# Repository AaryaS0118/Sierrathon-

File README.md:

# Sierrathon PCB Design – Pocket Lab

KiCad 10 project for the Sierrathon PCB design hackathon.
Pocket Lab: a keyring-sized USB logic analyzer / voltmeter for engineering students.
Specs, BOM and scoring live in `Resources/`.

## Board outline (done)
- Rounded stick, 75 x 27 mm, 3 mm corners. USB-C on BOTH ends:
  J1 (left, silkscreen "PC") goes to the laptop, J2 (right, silkscreen "PROBE") goes to the circuit under test.
- M4 holes sit right behind each USB-C so the screws take plug-in force:
  MH1/MH3 at (13, 6)/(13, 21), MH2/MH4 at (62, 6)/(62, 21). MH4 doubles as the keyring hole.
  Coordinates are mm from the board's top-left (grid origin is set there).
- Blue drawings on `User.Comments` are placement guides only (J1, J2, RP2040 zone, LED zone,
  R20-R25 zone, hole circles). Delete them once parts are placed.

## Probe port J2 (judges approved adding a USB-C)
J2 is the SAME part as J1 (UJ20-C-H-G-SMT-TR), so no new footprint. Each signal goes through
a 1 kΩ series resistor (R20-R25, same part as R7/R8: RC0402FR-071KL) placed close to J2.

| J2 pins | Net | RP2040 |
|---|---|---|
| A6 + B6 (D+, tied together) | CH0 | GPIO0 (pin 2) |
| A7 + B7 (D-, tied together) | CH1 | GPIO1 (pin 3) |
| A8 (SBU1) | CH2 | GPIO2 (pin 4) |
| B8 (SBU2) | CH3 | GPIO3 (pin 5) |
| A5 (CC1) | A0 | GPIO26 (pin 38) |
| B5 (CC2) | A1 | GPIO27 (pin 39) |
| GND pins + shell | GND | |
| VBUS pins | not connected (so a charger/laptop plugged in here can't push 5 V in) | |

Flipping the plug swaps CH2/CH3 and A0/A1 only. Draw J2 + R20-R25 on a second KiCad 10
top-level sheet and connect with **global** labels (CH0-CH3, A0, A1). On page 1 only GPIO0-3
and GPIO26-27 lose their no-connect X and get those labels.
BOM changes: USB-C line becomes J1, J2 qty 2; 1 kΩ line becomes R7, R8, R20-R25 qty 8.

## Team rules for working in this repo
- KiCad files don't merge well. **Only one person edits a given file at a time**
  (`.kicad_sch` = schematic, `.kicad_pcb` = board). Say so in the team chat before you start.
- Before you open KiCad: `git pull`. When you're done: save, close KiCad, then commit and push.
- Never commit while the file is open and unsaved.

## Design rules (already set up – don't change without telling the team)
- 4 layers, 62 mil, 1 oz copper, FR-370HR, green mask / white silk (Board Setup > Physical Stackup).
- Constraints page floors are 4 mil clearance / 5 mil track **on purpose**: they must equal the
  90 Ω USB pair geometry (5 mil trace, 4 mil gap). Everything else is held to 6 mil by net
  classes and by `Sierrathon-PCB Design.kicad_dru` (Board Setup > Custom Rules).
- Net classes: `USB_90R` (USB_P/N, USBR_P/N, D_P/D_N – use the diff-pair router, key `6`),
  `Power` (VBUS, +3.3V, +1.1V, GND – 15 mil), `Default` (8 mil).
- Net names in the schematic must match the PDF exactly or nets won't land in the right class.

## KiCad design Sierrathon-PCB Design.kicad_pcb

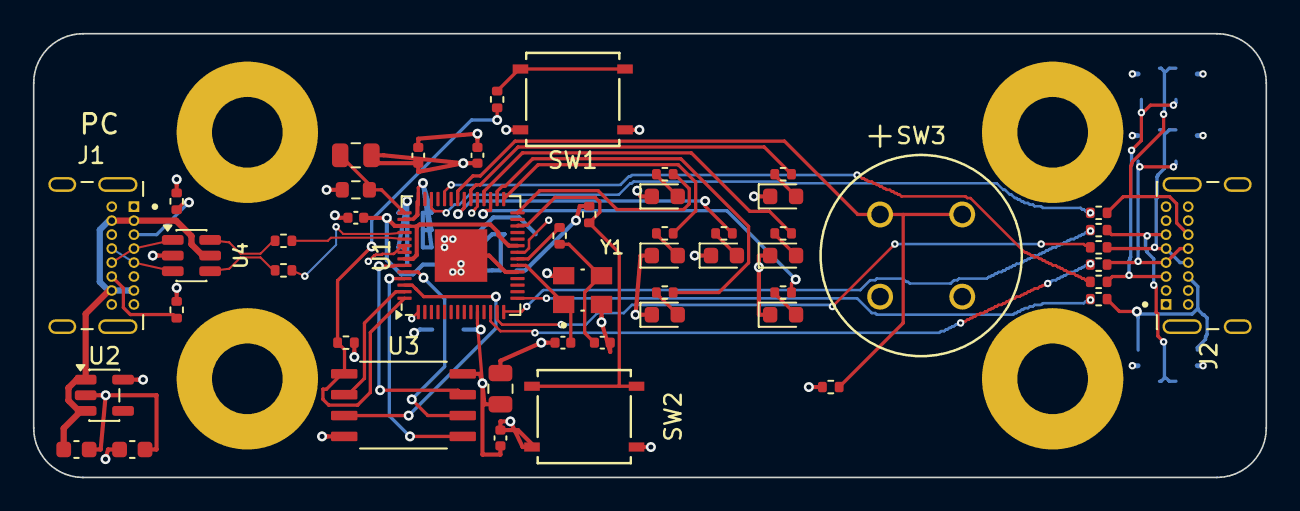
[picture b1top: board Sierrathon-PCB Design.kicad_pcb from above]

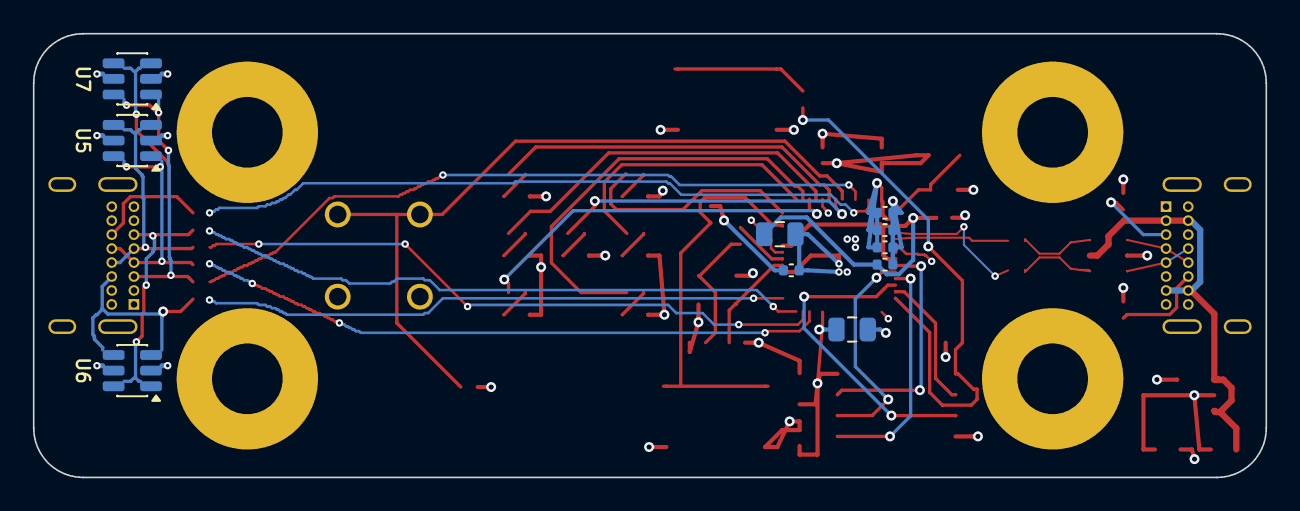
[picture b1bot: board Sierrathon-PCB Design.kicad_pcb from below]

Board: 4 copper layers, 75.0 x 27.0 mm, 64 parts (10 on the bottom side), 51 nets.

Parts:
C1, C2: 1uF; C_0603_1608Metric
C3, C5, C14, C17: 2.2uF; C_0805_2012Metric
C4, C8, C9, C10, C11, C12, C13, C15, C16: 0.1uF; C_0402_1005Metric
C6, C7: 15pF; C_0402_1005Metric
D3, D4, D5, D6, D7, D8, D9: LED; LED_0603_1608Metric
J1, J2: USB-C; CUI_UJ20-C-H-G-SMT-TR
MH1, MH2, MH3, MH4: Mounting Hole; MountingHole_4.3mm_M4_Pad
R1, R2: 5.1K; R_0402_1005Metric
R4: 200; R_0603_1608Metric
R5, R6: 27; R_0402_1005Metric
R7, R8, R20, R21, R22, R23, R24, R25: 1K; R_0402_1005Metric
R9, R10, R19: 10K; R_0402_1005Metric
R12, R13, R14, R15, R16, R17, R18: 330; R_0402_1005Metric
SW1: BOOT; SON4_PTS526 SM15 SMTR2 LFS_CNK
SW2: RESET; SON4_PTS526 SM15 SMTR2 LFS_CNK
SW3: SWITCH; D6R90_CNK
U1: RP2040; QFN-56-1EP_7x7mm_P0.4mm_EP3.2x3.2mm
U2: AP2112; SOT-23-5
U3: W25Q128JVSIQ; SOIC127P790X216-8N
U4, U5, U6, U7: USBLC6-2SC6; SOT-23-6
Y1: CRYSTAL14; XTAL_ABM8-272-T3

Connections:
+1.1V: C15.2, C16.2, C17.2, U1.23 (DVDD), U1.45 (VREG_VOUT), U1.50 (DVDD)
+3.3V: C2.1, C3.1, C4.1, C8.2, C9.2, C10.2, C11.2, C12.2, C13.2, C14.2, R4.1, R9.2, R10.2, R19.1, U1.1 (IOVDD), U1.10 (IOVDD), U1.22 (IOVDD), U1.33 (IOVDD), U1.42 (IOVDD), U1.44 (VREG_VIN), U1.48 (USB_VDD), U1.49 (IOVDD), U2.5 (VOUT), U3.8, U5.5 (VBUS), U6.5 (VBUS), U7.5 (VBUS)
/A0: R24.2, U1.38 (GPIO26/ADC0)
/A1: R25.2, U1.40 (GPIO28/ADC2)
/BOOT: R8.2, SW1.1, SW1.2
/CH0: R20.2, U1.12 (GPIO9)
/CH1: R21.2, U1.13 (GPIO10)
/CH2: R22.2, U1.14 (GPIO11)
/CH3: R23.2, U1.15 (GPIO12)
/D_N: J1.A7, J1.B7, U4.3 (I/O2)
/D_P: J1.A6, J1.B6, U4.1 (I/O1)
/Led1: R12.2, U1.28 (GPIO17)
/Led2: R13.2, U1.29 (GPIO18)
/Led3: R14.2, U1.30 (GPIO19)
/Led4: R15.2, U1.31 (GPIO20)
/Led5: R16.2, U1.32 (GPIO21)
/Led6: R17.2, U1.34 (GPIO22)
/Led7: R18.2, U1.35 (GPIO23)
/P_CC1: J2.A5, R24.1, U7.1 (I/O1), U7.6 (I/O1)
/P_CC2: J2.B5, R25.1, U7.3 (I/O2), U7.4 (I/O2)
/P_DN: J2.A7, J2.B7, R21.1, U5.3 (I/O2), U5.4 (I/O2)
/P_DP: J2.A6, J2.B6, R20.1, U5.1 (I/O1), U5.6 (I/O1)
/P_SBU1: J2.A8, R22.1, U6.1 (I/O1), U6.6 (I/O1)
/P_SBU2: J2.B8, R23.1, U6.3 (I/O2), U6.4 (I/O2)
/QSPI_CLK: U1.52 (QSPI_SCLK), U3.6
/QSPI_CS: R8.1, R9.1, U1.56 (~QSPI_SS), U3.1
/QSPI_D0: U1.53 (QSPI_SD0), U3.5
/QSPI_D1: U1.55 (QSPI_SD1), U3.2
/QSPI_D2: U1.54 (QSPI_SD2), U3.3
/QSPI_D3: U1.51 (QSPI_SD3), U3.7
/RESET: R10.1, SW2.1, SW2.2, U1.26 (RUN)
/SW: R19.2, SW3.1, SW3.2, U1.36 (GPIO24)
/USBR_N: R5.2, U1.46 (USB_DM)
/USBR_P: R6.2, U1.47 (USB_DP)
/USB_N: R5.1, U4.4 (I/O2)
/USB_P: R6.1, U4.6 (I/O1)
GND: C1.2, C2.2, C3.2, C4.2, C5.2, C6.1, C7.2, C8.1, C9.1, C10.1, C11.1, C12.1, C13.1, C14.1, C15.1, C16.1, C17.1, D3.1 (K), D4.1 (K), D5.1 (K), D6.1 (K), D7.1 (K), D8.1 (K), D9.1 (K), J1.A1, J1.A12, J1.B1, J1.B12, J1.SH1, J1.SH2, J1.SH3, J1.SH4, J2.A1, J2.A12, J2.B1, J2.B12, J2.SH1, J2.SH2, J2.SH3, J2.SH4, MH1.1 (1_1), MH2.1 (1_1), MH3.1 (1_1), MH4.1 (1_1), R1.2, R2.2, SW1.3, SW1.4, SW2.3, SW2.4, SW3.3, SW3.4, U1.19 (TESTEN), U1.57 (GND), U2.2 (GND), U3.4, U4.2 (GND), U5.2 (GND), U6.2 (GND), U7.2 (GND), Y1.2, Y1.4
unnamed: C7.1, R7.1, Y1.3
unnamed: D3.2 (A), R12.1
unnamed: D4.2 (A), R13.1
unnamed: D5.2 (A), R14.1
unnamed: D6.2 (A), R15.1
unnamed: D7.2 (A), R16.1
unnamed: D8.2 (A), R17.1
unnamed: D9.2 (A), R18.1
unnamed: J1.A5, R1.1
unnamed: J1.B5, R2.1
unnamed: C5.1, R4.2, U1.43 (ADC_AVDD)
unnamed: C6.2, U1.20 (XIN), Y1.1
unnamed: R7.2, U1.21 (XOUT)
VBUS: C1.1, J1.A4, J1.A9, J1.B4, J1.B9, U2.1 (VIN), U2.3 (EN), U4.5 (VBUS)

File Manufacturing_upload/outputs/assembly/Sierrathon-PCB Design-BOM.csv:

"Reference","Value","Footprint","Qty","MPN","Manufacturer","Description","DNP"
"C1,C2","1uF","Capacitor_SMD:C_0603_1608Metric","2","GCM188R71C105KA64D","Murata Electronics","Unpolarized capacitor",""
"C3,C5,C14,C17","2.2uF","Capacitor_SMD:C_0805_2012Metric","4","GCM21BR71C225KA64L","Murata Electronics","Unpolarized capacitor",""
"C4,C8-C13,C15,C16","0.1uF","Capacitor_SMD:C_0402_1005Metric","9","GCM155R71C104KA55D","Murata Electronics","Unpolarized capacitor",""
"C6,C7","15pF","Capacitor_SMD:C_0402_1005Metric","2","GCM1555C1H150JA16D","Murata Electronics","Unpolarized capacitor",""
"D3-D9","LED","LED_SMD:LED_0603_1608Metric","7","QBLP601-R5","QT Brightek (QTB)","Light emitting diode",""
"J1,J2","USB-C","Sierrathon:CUI_UJ20-C-H-G-SMT-TR","2","UJ20-C-H-G-SMT-TR","Same Sky (Formerly CUI Devices)","Type C, USB 2.0, 480 Mbps, 20 Vdc, 5 A, Right Angle, Gold Flash, Surface Mount, Black Insulator, USB Receptacle",""
"MH1-MH4","Mounting Hole","MountingHole:MountingHole_4.3mm_M4_Pad","4","","","Mounting Hole with connection","DNP"
"R1,R2","5.1K","Resistor_SMD:R_0402_1005Metric","2","RC0402JR-075K1L","YAGEO","Resistor, US symbol",""
"R4","200","Resistor_SMD:R_0603_1608Metric","1","RC0603JR-07200RL","YAGEO","Resistor, US symbol",""
"R5,R6","27","Resistor_SMD:R_0402_1005Metric","2","RC0402FR-0727RL","YAGEO","Resistor, US symbol",""
"R7,R8,R20-R25","1K","Resistor_SMD:R_0402_1005Metric","8","RC0402FR-071KL","YAGEO","Resistor, US symbol",""
"R9,R10,R19","10K","Resistor_SMD:R_0402_1005Metric","3","RC0402JR-0710KL","YAGEO","Resistor, US symbol",""
"R12-R18","330","Resistor_SMD:R_0402_1005Metric","7","AF0402JR-07330RL","YAGEO","Resistor, US symbol",""
"SW1","BOOT","Sierrathon:SON4_PTS526 SM15 SMTR2 LFS_CNK","1","PTS526SM15SMTR2 LFS","C&K","",""
"SW2","RESET","Sierrathon:SON4_PTS526 SM15 SMTR2 LFS_CNK","1","PTS526SM15SMTR2 LFS","C&K","",""
"SW3","SWITCH","Sierrathon:D6R90_CNK","1","D6R90 F2 LFS","C&K","",""
"U1","RP2040","Package_DFN_QFN:QFN-56-1EP_7x7mm_P0.4mm_EP3.2x3.2mm","1","SC0914(13)","Raspberry Pi","A microcontroller by Raspberry Pi, Dual ARM Cortex-M0+, 133MHz, no flash, 264KB SRAM, 8 PIO state machines, VQFN-56",""
"U2","AP2112","Package_TO_SOT_SMD:SOT-23-5","1","AP2112K-3.3TRG1","Diodes Incorporated","600mA low dropout linear regulator, with enable pin, 3.8V-6V input voltage range, 3.3V fixed positive output, SOT-23-5",""
"U3","W25Q128JVSIQ","Sierrathon:SOIC127P790X216-8N","1","W25Q128JVSIQ TR","Winbond Electronics","FLASH - NOR Memory IC 128Mb (16M x 8) SPI - Quad I/O, QPI, DTR 133 MHz 8-SOIC",""
"U4-U7","USBLC6-2SC6","Package_TO_SOT_SMD:SOT-23-6","4","USBLC6-2SC6","STMicroelectronics","Very low capacitance ESD protection diode, 2 data-line, SOT-23-6",""
"Y1","CRYSTAL14","Sierrathon:XTAL_ABM8-272-T3","1","ABM8-272-T3","Abracon LLC","12 MHz ±30ppm Crystal 10pF 50 Ohms 4-SMD, No Lead",""
